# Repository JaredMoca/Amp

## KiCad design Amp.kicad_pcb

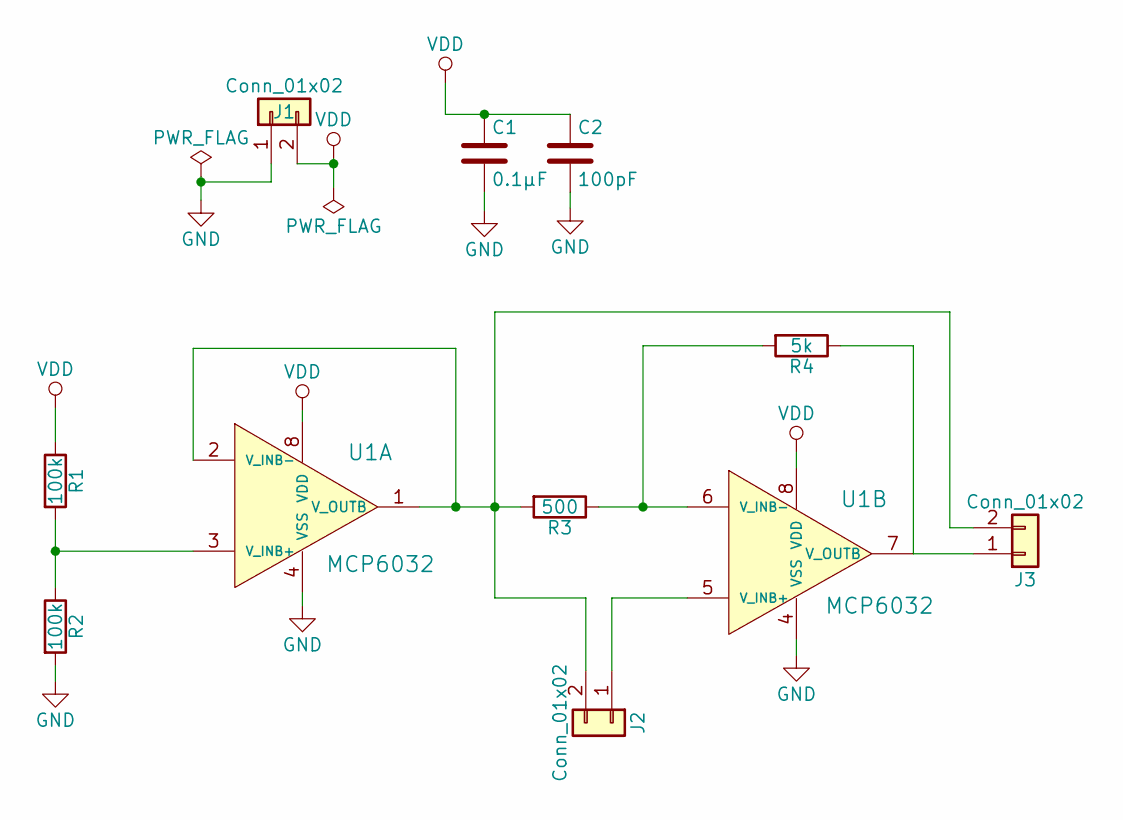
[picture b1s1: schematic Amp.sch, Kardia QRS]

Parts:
C1: 0.1μF; C_1206_HandSoldering
C2: 100pF; C_1206_HandSoldering
J1, J2, J3: Conn_01x02; JST_XH_S02B-XH-A_02x2.50mm_Angled
R1, R2: 100k; R_1206_HandSoldering
R3: 500; R_1206_HandSoldering
R4: 5k; R_1206_HandSoldering
U1: MCP6032; SOIC127P600X175-8N

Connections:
GND: C1.2, C2.2, J1.1, R2.2, U1.4 (VSS)
unnamed: J2.1, U1.5 (V_INB+)
unnamed: J2.2, J3.2, R3.2, U1.1 (V_OUTB), U1.2 (V_INB-)
unnamed: J3.1, R4.1, U1.7 (V_OUTB)
unnamed: R1.2, R2.1, U1.3 (V_INB+)
unnamed: R3.1, R4.2, U1.6 (V_INB-)
VDD: C1.1, C2.1, J1.2, R1.1, U1.8 (VDD)

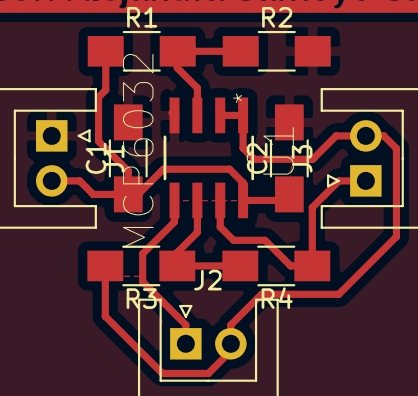
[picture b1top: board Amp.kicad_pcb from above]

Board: 2 copper layers, 11 parts (0 on the bottom side), 7 nets.

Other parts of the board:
n***: names

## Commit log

2019-04-19 ECG signal amplifier

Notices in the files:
Amp.kicad_pcb:
License: CC BY-NC-SA
Amp.sch:
creativecommons.org/licenses/by-nc-sa/4.0
